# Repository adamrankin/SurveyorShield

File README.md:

# SurveyorShield
A repository containing the files relating to a shield purpose built to survey using barometric altitude and GPS information.

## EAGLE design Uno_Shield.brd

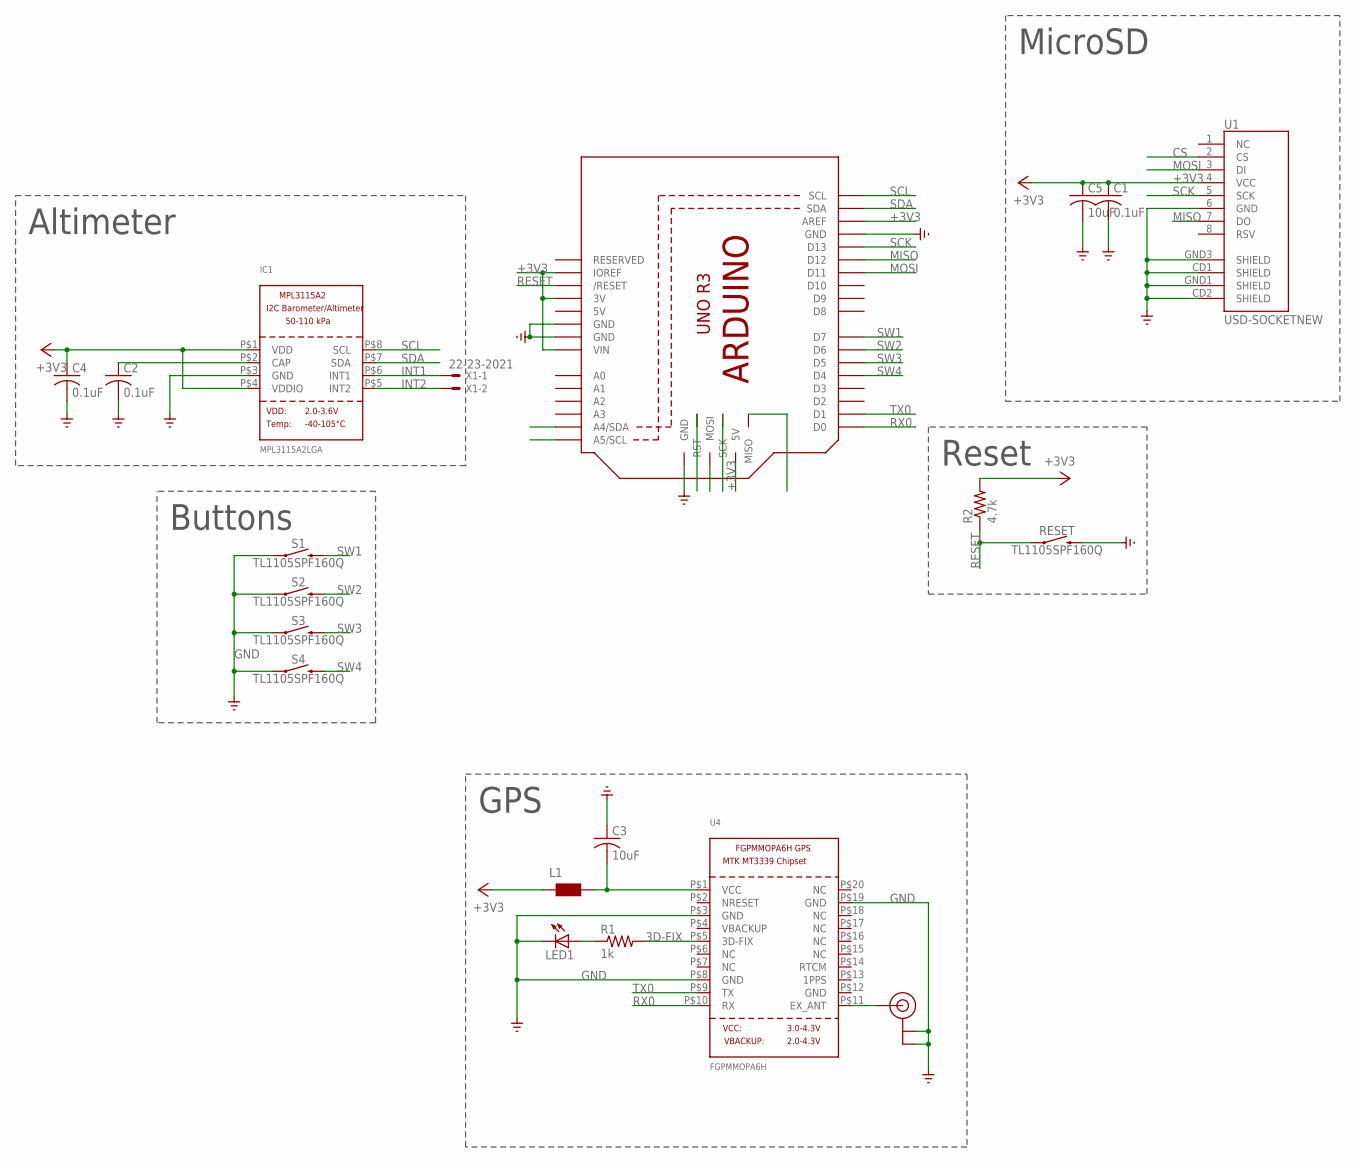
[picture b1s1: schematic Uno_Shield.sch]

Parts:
C1, C2, C4: 0.1uF; C1206
C3, C5: 10uF; C1206
IC1: MPL3115A2LGA; LGA8
L1: WE-CBF_1206; 1206
LED1: LEDSMT1206; 1206
M1: ARDUINO_R3_ICSP; ARDUINOR3_ICSP
R1: 1k; R1206
R2: 4.7k; R1206
RESET: TL1105SPF160Q; TACTILE_SWITCH_PTH_6.0MM
S1, S2, S3, S4: TL1105SPF160Q; TACTILE_SWITCH_PTH_6.0MM
U1: USD-SOCKETNEW; MICRO-SD-SOCKET-PP
U4: FGPMMOPA6H
U$20: U.FL
X1: 22-23-2021

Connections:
3D-FIX: R1.2, U4.P$5 (3D-FIX)
3D-FIX_R: LED1.A, R1.1
3V3_CLEAN: C3.2, L1.2, U4.P$1 (VCC)
5V: M1.5V
+3V3: C1.1, C4.1, C5.1, IC1.P$1 (VDD), IC1.P$4 (VDDIO), L1.1, M1.3V, M1.5V_ICSP (5V), M1.AREF, M1.IOREF, M1.VIN, R2.2, U1.4 (VCC)
CAP: C2.1, IC1.P$2 (CAP)
CS: U1.2 (CS)
EX_ANT: U4.P$11 (EX_ANT), U$20.P$3 (SIGNAL)
GND: C1.2, C2.2, C3.1, C4.2, C5.2, IC1.P$3 (GND), LED1.C, M1.GND, M1.GND@1 (GND), M1.GND@2 (GND), M1.GND@3 (GND), RESET.3 (2), S1.1, S2.1, S3.1, S4.1, U1.6 (GND), U1.CD1 (SHIELD), U1.CD2 (SHIELD), U1.GND1 (SHIELD), U1.GND3 (SHIELD), U4.P$3 (GND), U4.P$8 (GND), U4.P$19 (GND), U$20.P$1 (GND), U$20.P$2 (GND)
INT1: IC1.P$6 (INT1), X1.1
INT2: IC1.P$5 (INT2), X1.2
MISO: M1.D12, M1.MISO, U1.7 (DO)
MOSI: M1.D11, M1.MOSI, U1.3 (DI)
RESET: M1.RESET (/RESET), M1.RESET_ICSP (RST), R2.1, RESET.1
RX0: M1.D0, U4.P$10 (RX)
SCK: M1.D13, M1.SCK, U1.5 (SCK)
SCL: IC1.P$8 (SCL), M1.A5 (A5/SCL), M1.SCL
SDA: IC1.P$7 (SDA), M1.A4 (A4/SDA), M1.SDA
SW1: M1.D7, S1.3 (2)
SW2: M1.D6, S2.3 (2)
SW3: M1.D5, S3.3 (2)
SW4: M1.D4, S4.3 (2)
TX0: M1.D1, U4.P$9 (TX)

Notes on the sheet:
Altimeter
MicroSD
GPS
Buttons
Reset

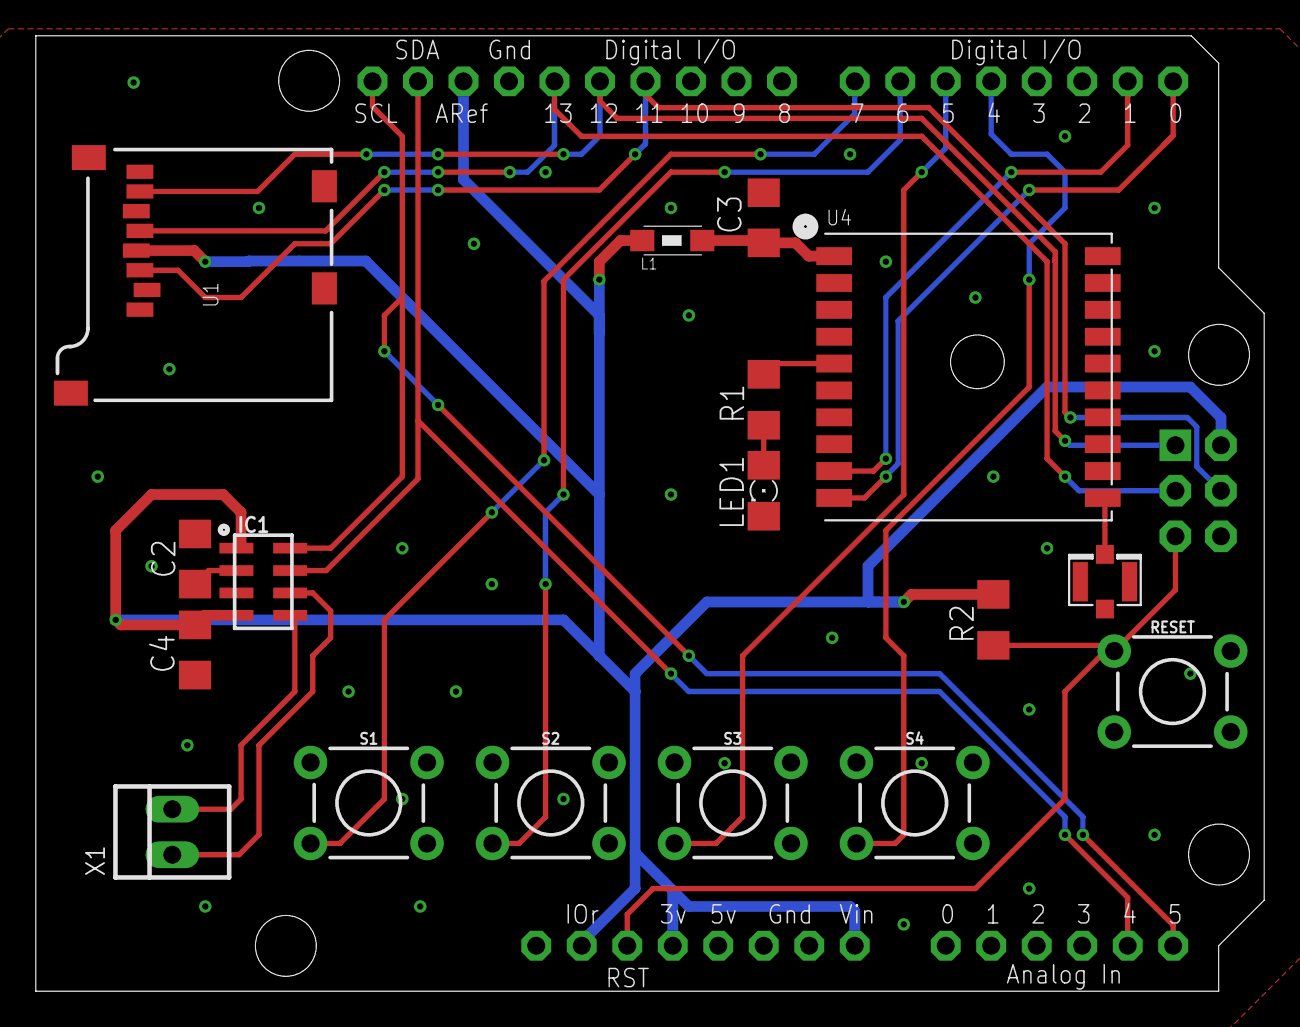
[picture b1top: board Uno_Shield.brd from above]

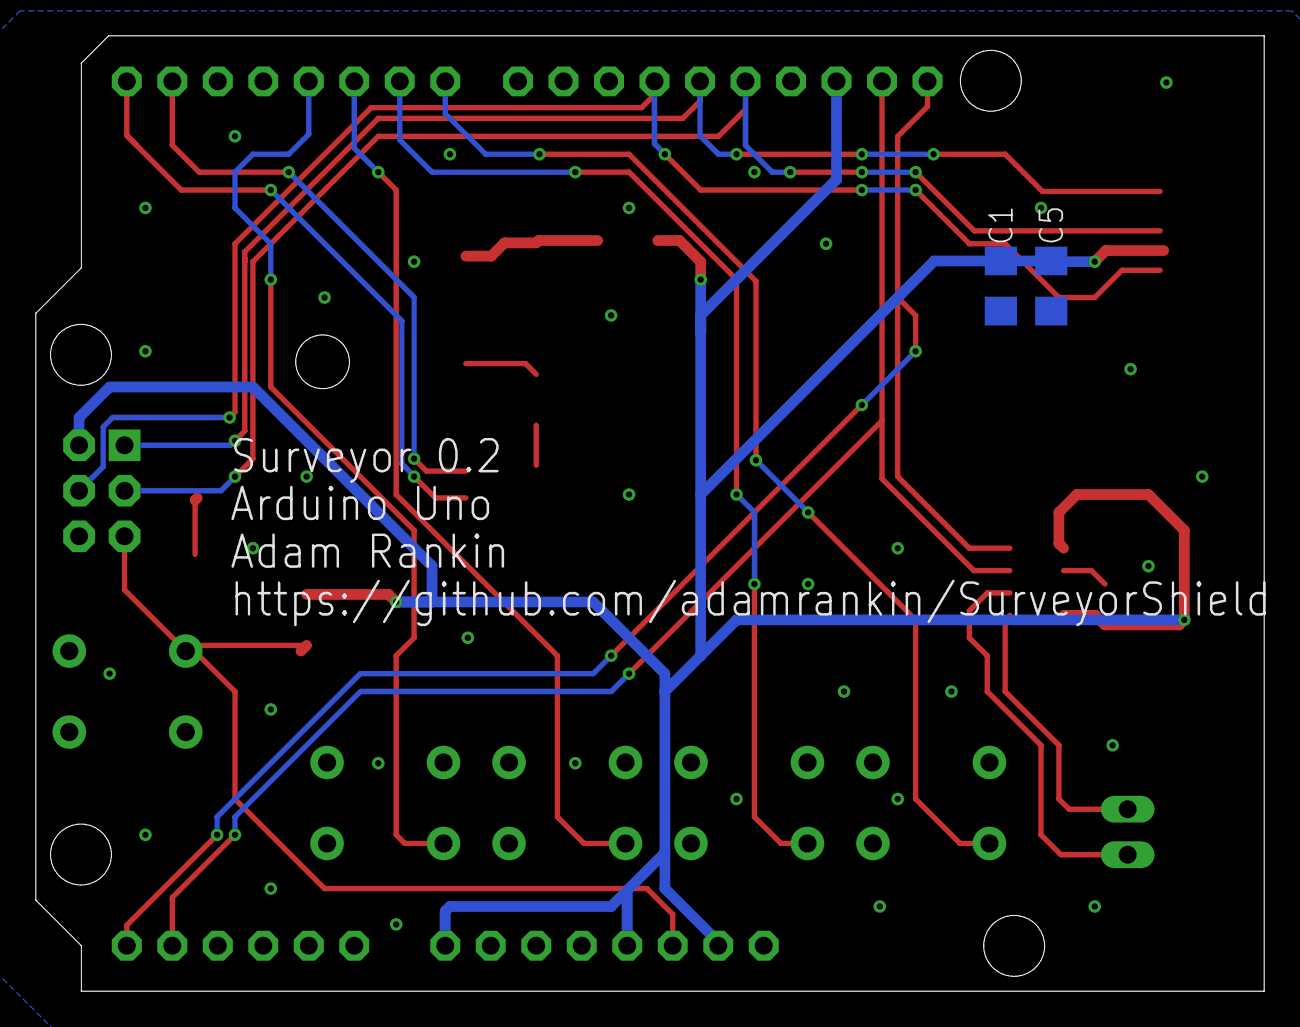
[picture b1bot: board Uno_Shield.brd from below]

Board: 2 copper layers, 68.6 x 53.3 mm, 20 parts (2 on the bottom side), 21 nets.

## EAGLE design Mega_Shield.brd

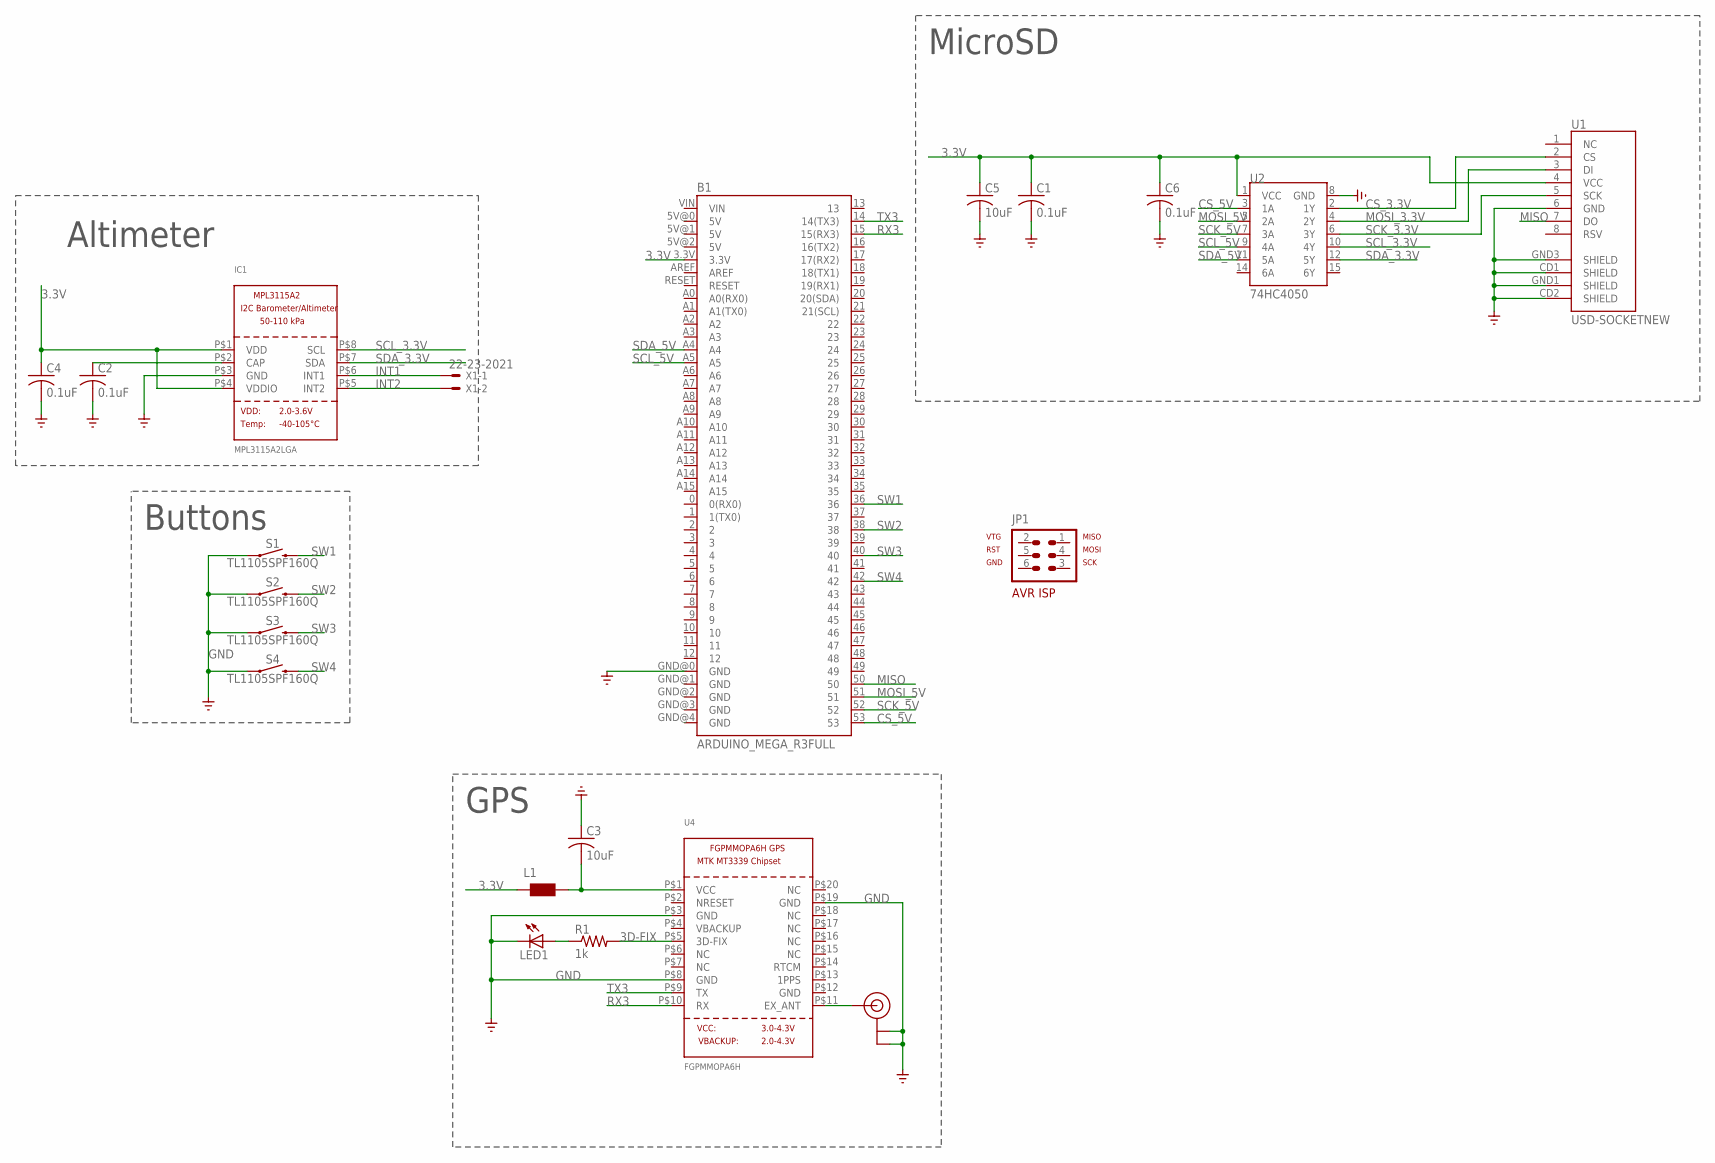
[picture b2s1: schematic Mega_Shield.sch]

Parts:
B1: ARDUINO_MEGA_R3FULL; ARDUINO_MEGA
C1, C2, C4, C6: 0.1uF; C1206
C3, C5: 10uF; C1206
IC1: MPL3115A2LGA; LGA8
JP1: AVR-ISP-6
L1: WE-CBF_1206; 1206
LED1: LEDSMT1206; 1206
R1: 1k; R1206
S1, S2, S3, S4: TL1105SPF160Q; TACTILE_SWITCH_PTH_6.0MM
U1: USD-SOCKETNEW; MICRO-SD-SOCKET-PP
U2: 74HC4050; SO16
U4: FGPMMOPA6H
U$20: U.FL
X1: 22-23-2021

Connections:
3.3V: B1.3.3V, C1.1, C4.1, C5.1, C6.1, IC1.P$1 (VDD), IC1.P$4 (VDDIO), L1.1, U1.4 (VCC), U2.1 (VCC)
3D-FIX: R1.2, U4.P$5 (3D-FIX)
3D-FIX_R: LED1.A, R1.1
3V3_CLEAN: C3.2, L1.2, U4.P$1 (VCC)
CAP: C2.1, IC1.P$2 (CAP)
CS_3.3V: U1.2 (CS), U2.2 (1Y)
CS_5V: B1.53, U2.3 (1A)
EX_ANT: U4.P$11 (EX_ANT), U$20.P$3 (SIGNAL)
GND: B1.GND@0 (GND), C1.2, C2.2, C3.1, C4.2, C5.2, C6.2, IC1.P$3 (GND), LED1.C, S1.1, S2.1, S3.1, S4.1, U1.6 (GND), U1.CD1 (SHIELD), U1.CD2 (SHIELD), U1.GND1 (SHIELD), U1.GND3 (SHIELD), U2.8 (GND), U4.P$3 (GND), U4.P$8 (GND), U4.P$19 (GND), U$20.P$1 (GND), U$20.P$2 (GND)
INT1: IC1.P$6 (INT1), X1.1
INT2: IC1.P$5 (INT2), X1.2
MISO: B1.50, U1.7 (DO)
MOSI_3.3V: U1.3 (DI), U2.4 (2Y)
MOSI_5V: B1.51, U2.5 (2A)
RX3: B1.15 (15(RX3)), U4.P$10 (RX)
SCK_3.3V: U1.5 (SCK), U2.6 (3Y)
SCK_5V: B1.52, U2.7 (3A)
SCL_3.3V: IC1.P$8 (SCL), U2.10 (4Y)
SCL_5V: B1.A5, U2.9 (4A)
SDA_3.3V: IC1.P$7 (SDA), U2.12 (5Y)
SDA_5V: B1.A4, U2.11 (5A)
SW1: B1.36, S1.3 (2)
SW2: B1.38, S2.3 (2)
SW3: B1.40, S3.3 (2)
SW4: B1.42, S4.3 (2)
TX3: B1.14 (14(TX3)), U4.P$9 (TX)

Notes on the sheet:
Altimeter
MicroSD
GPS
Buttons

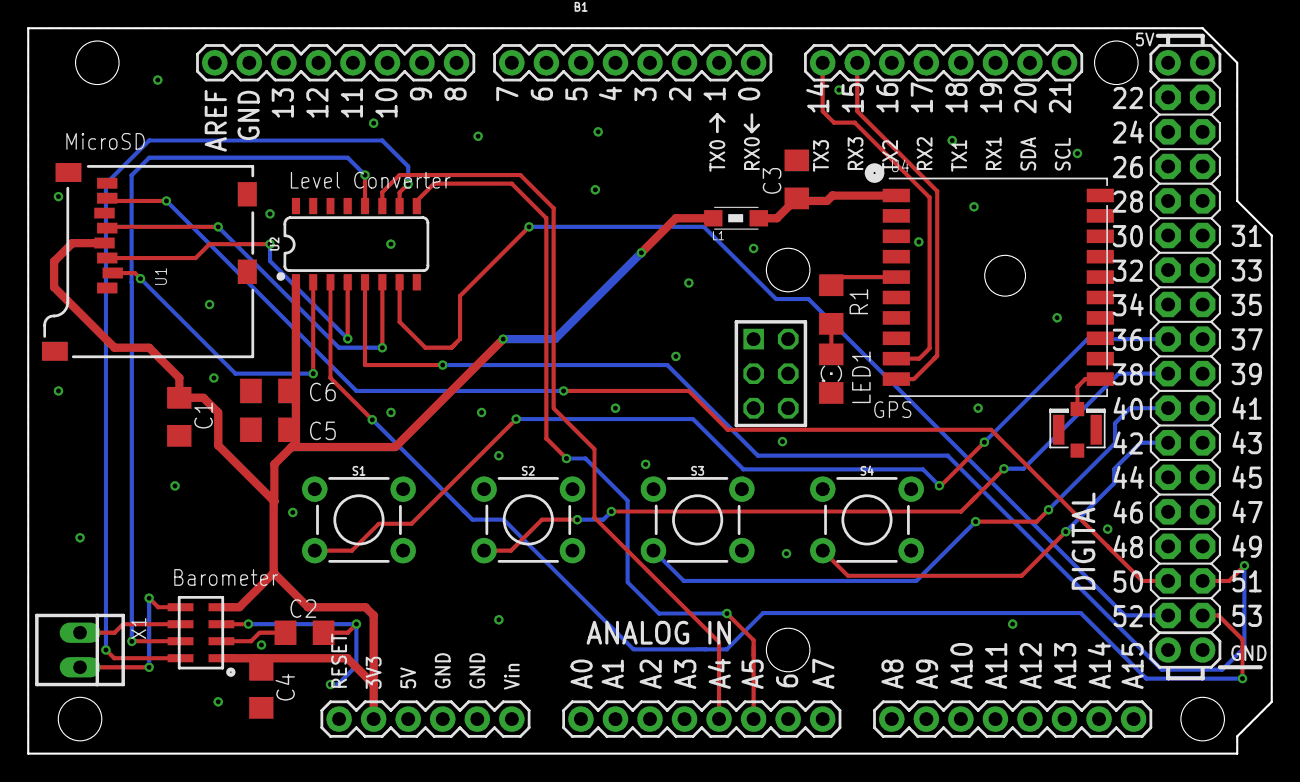
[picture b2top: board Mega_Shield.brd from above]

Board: 2 copper layers, 91.4 x 53.3 mm, 21 parts (0 on the bottom side), 26 nets.

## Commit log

2017-07-09 Adding Arduino code
    Currently written for Arduino Mega
2017-08-13 Updating board layout adding button controls
2017-08-13 Updating project
2017-10-13 Updated design
2017-10-13 Rev 0.2
    Uno edition
    Mega edition
    Individual switches (cheaper, replacable!)

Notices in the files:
parts and their libraries:
SparkFun-Boards: Licensing: Creative Commons ShareAlike 4.0 International - https://creativecommons.org/licenses/by-sa/4.0
wuerth-elektronik: Copyright: Würth Elektronik eiSos
